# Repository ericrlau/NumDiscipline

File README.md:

# #DISCIPLINE (aka NumDiscipline)

A modified version of the great looking Discipline through hole keyboard design by coseyfannitutti to add numpad. 

## Modifications from original Discipline 

- Add numpad on right.
- Move arrow keys 0.25U down and right, similar to 1800 layout. 
- Adjust component layout on top of board, moving ATMega and buttons to the right, adding in more diodes in center. 
- Removed ~, Delete, Page Up, Page Down keys. These will be on alternate layer. 
- Created Digikey version of BOM, found here: https://octopart.com/bom-tool/AgAHKWUi

## ToDo 
- Adjust acrylic foot design to be wider, it looks a little thin. 
- add Via support
- Next order of PCBs: 
	- Adjust #DISCIPLINE logo in space bar area so that it doesn't overlap stablaizer. [Image](./images/knownIssues/Logoplacement.jpg)
	- Omit job number silk screen from vendor.[Plate](./images/knownIssues/plate.jpg) [Main](./images/knownIssues/jobNumMain.jpg) [Bottom](./images/knownIssues/jobNumBottom.jpg) 
	- Improve surface finish on black solder mask, some dark spots. [Image](./images/knownIssues/surfaceFinish.jpg) 
	- Remove drills from FR4 switch plate. [Image](./images/knownIssues/plate.jpg)

## Images

#### Prototype Build

#### Layout

#### Main PCB

#### FR4 Plate

#### Bottom PCB

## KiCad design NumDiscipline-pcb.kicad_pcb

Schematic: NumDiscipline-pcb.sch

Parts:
BOOT1: BOOT; SW_PUSH_6mm
C1, C2: 22p; C_Disc_D3.0mm_W1.6mm_P2.50mm
C3: 4.7u; CP_Radial_D4.0mm_P1.50mm
C4, C5: 0.1u; D_DO-35_SOD27_P5.08mm_Horizontal
D1, D2, D3, D4, D5, D6, D7, D8, D9, D10, D11, D12, D13, D14, D15, D16, D17, D18, D19, D20, D21, D22, D23, D24, D25, D26, D27, D28, D29, D30, D31, D32, D33, D34, D35, D36, D37, D38, D39, D40, D41, D42, D43, D44, D45, D46, D47, D48, D49, D50, D51, D52, D53, D54, D55, D56, D57, D58, D59, D60, D61, D62, D63, D64, D65, D66, D67, D68, D75, D76, D77, D78, D79, D80, D81, D82, D83, D84, D85, D86, D87: D_DO-35_SOD27_P5.08mm_Horizontal
D69, D70: 3.6V; D_DO-35_SOD27_P5.08mm_Horizontal
F1: 500mA; polyfuse_5.1mm
J1: AVR-ISP-6; AVR_ICSP_3x2
LED1: POWER; LED_D3.0mm
R1, R2: 5.1k; R_Axial_DIN0204_L3.6mm_D1.6mm_P7.62mm_Horizontal
R3, R4: 75R; R_Axial_DIN0204_L3.6mm_D1.6mm_P7.62mm_Horizontal
R5: 1.5k; R_Axial_DIN0204_L3.6mm_D1.6mm_P7.62mm_Horizontal
R6: 1.5K; R_Axial_DIN0204_L3.6mm_D1.6mm_P7.62mm_Horizontal
R7: 10k; R_Axial_DIN0204_L3.6mm_D1.6mm_P7.62mm_Horizontal
RESET1: RESET; SW_PUSH_6mm
SW1: ESCAPE; SW_Cherry_MX1A_1.00u_PCB-NOSCREEN
SW2: 1; SW_Cherry_MX1A_1.00u_PCB-NOSCREEN
SW3, SW4, SW5, SW6, SW7, SW8, SW9, SW10, SW11, SW12, SW13, SW15, SW17, SW18, SW19, SW20, SW21, SW22, SW23, SW24, SW25, SW26, SW27, SW28, SW30, SW32, SW33, SW34, SW35, SW36, SW37, SW38, SW39, SW40, SW41, SW42, SW44, SW46, SW47, SW48, SW49, SW50, SW51, SW52, SW53, SW54, SW55, SW57, SW58, SW62, SW65, SW66, SW67, SW68, SW72, SW75, SW76, SW77, SW78, SW79, SW81, SW82, SW83, SW84, SW86, SW87: KEYSW; SW_Cherry_MX1A_1.00u_PCB-NOSCREEN
SW14, SW80, SW85: KEYSW; SW_Cherry_MX1A_2.00u_PCBNOSCREEN
SW16, SW29, SW70, SW71, SW73, SW74: KEYSW; SW_Cherry_MX1A_1.50u_PCBNOSCREEN
SW31, SW56: KEYSW; SW_Cherry_MX1A_1.75u_PCBNOSCREEN
SW43, SW45: KEYSW; SW_Cherry_MX1A_2.25u_PCBNOSCREEN
SW59, SW60, SW61, SW63, SW64, SW69: KEYSW; SW_Cherry_MX1A_1.25u_PCBNOSCREEN
U1: ATmega32A-PU; DIP-40_W15.24mm
USB1: USB_C_GCT_USB4085
Y1: Crystal; Crystal_HC49-4H_Vertical

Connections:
+5V: C3.1, C4.1, C5.1, F1.1, J1.2, LED1.2 (A), R5.1, R7.1, U1.10, U1.30
D+: R4.1, U1.16
D-: R3.1, U1.17
GND: BOOT1.1, C1.2, C2.2, C3.2, C4.2, C5.2, D69.2 (A), D70.2 (A), J1.6, R1.1, R2.2, R6.2, RESET1.1, U1.11, U1.31, USB1.A1, USB1.A12, USB1.B1, USB1.B12, USB1.S1
MISO: J1.1, U1.7
MOSI: J1.4, U1.6
unnamed: C1.1, U1.13, Y1.1
unnamed: C2.1, U1.12, Y1.2
unnamed: D1.2 (A), SW1.2
unnamed: D2.2 (A), SW2.2
unnamed: D3.2 (A), SW3.2
unnamed: D4.2 (A), SW4.2
unnamed: D5.2 (A), SW5.2
unnamed: D6.2 (A), SW6.2
unnamed: D7.2 (A), SW7.2
unnamed: D8.2 (A), SW8.2
unnamed: D9.2 (A), SW9.2
unnamed: D10.2 (A), SW10.2
unnamed: D11.2 (A), SW11.2
unnamed: D12.2 (A), SW12.2
unnamed: D13.2 (A), SW13.2
unnamed: D14.2 (A), SW14.2
unnamed: D15.2 (A), SW15.2
unnamed: D16.2 (A), SW16.2
unnamed: D17.2 (A), SW17.2
unnamed: D18.2 (A), SW18.2
unnamed: D19.2 (A), SW19.2
unnamed: D20.2 (A), SW20.2
unnamed: D21.2 (A), SW21.2
unnamed: D22.2 (A), SW22.2
unnamed: D23.2 (A), SW23.2
unnamed: D24.2 (A), SW24.2
unnamed: D25.2 (A), SW25.2
unnamed: D26.2 (A), SW26.2
unnamed: D27.2 (A), SW27.2
unnamed: D28.2 (A), SW28.2
unnamed: D29.2 (A), SW29.2
unnamed: D30.2 (A), SW30.2
unnamed: D31.2 (A), SW31.2, SW69.2
unnamed: D32.2 (A), SW32.2
unnamed: D33.2 (A), SW33.2
unnamed: D34.2 (A), SW34.2
unnamed: D35.2 (A), SW35.2
unnamed: D36.2 (A), SW36.2
unnamed: D37.2 (A), SW37.2
unnamed: D38.2 (A), SW38.2
unnamed: D39.2 (A), SW39.2
unnamed: D40.2 (A), SW40.2
unnamed: D41.2 (A), SW41.2
unnamed: D42.2 (A), SW42.2
unnamed: D43.2 (A), SW43.2
unnamed: D44.2 (A), SW44.2
unnamed: D45.2 (A), SW45.2
unnamed: D46.2 (A), SW46.2
unnamed: D47.2 (A), SW47.2
unnamed: D48.2 (A), SW48.2
unnamed: D49.2 (A), SW49.2
unnamed: D50.2 (A), SW50.2
unnamed: D51.2 (A), SW51.2
unnamed: D52.2 (A), SW52.2
unnamed: D53.2 (A), SW53.2
unnamed: D54.2 (A), SW54.2
unnamed: D55.2 (A), SW55.2
unnamed: D56.2 (A), SW56.2
unnamed: D57.2 (A), SW57.2
unnamed: D58.2 (A), SW58.2
unnamed: D59.2 (A), SW59.2, SW70.2
unnamed: D60.2 (A), SW60.2
unnamed: D61.2 (A), SW61.2, SW71.2
unnamed: D62.2 (A), SW62.2, SW72.2
unnamed: D63.2 (A), SW63.2, SW73.2
unnamed: D64.2 (A), SW64.2, SW74.2
unnamed: D65.2 (A), SW65.2
unnamed: D66.2 (A), SW66.2
unnamed: D67.2 (A), SW67.2
unnamed: D68.2 (A), SW68.2
unnamed: D69.1 (K), R3.2, R5.2, USB1.A7, USB1.B7
unnamed: D70.1 (K), R4.2, USB1.A6, USB1.B6
unnamed: D75.2 (A), SW75.2
unnamed: D76.2 (A), SW76.2
unnamed: D77.2 (A), SW77.2
unnamed: D78.2 (A), SW78.2
unnamed: D79.2 (A), SW79.2
unnamed: D80.2 (A), SW80.2
unnamed: D81.2 (A), SW81.2
unnamed: D82.2 (A), SW82.2
unnamed: D83.2 (A), SW83.2
unnamed: D84.2 (A), SW84.2
unnamed: D85.2 (A), SW85.2
unnamed: D86.2 (A), SW86.2
unnamed: D87.2 (A), SW87.2
unnamed: LED1.1 (K), R6.1
unnamed: R1.2, USB1.A5
unnamed: R2.1, USB1.B5
SCK: J1.3, U1.8
VCC: F1.2, USB1.A4, USB1.A9, USB1.B4, USB1.B9
boot: BOOT1.2, U1.18
col0: SW1.1, SW16.1, SW31.1, SW45.1, SW59.1, SW69.1, SW70.1, U1.38
col1: SW2.1, SW17.1, SW32.1, SW60.1, U1.4
col2: SW3.1, SW18.1, SW33.1, SW46.1, SW61.1, SW71.1, U1.37
col3: SW4.1, SW19.1, SW34.1, SW47.1, U1.5
col4: SW5.1, SW20.1, SW35.1, SW48.1, U1.36
col5: SW6.1, SW21.1, SW36.1, SW49.1, U1.19
col6: SW7.1, SW22.1, SW37.1, SW50.1, SW62.1, SW72.1, U1.20
col7: SW8.1, SW23.1, SW38.1, SW51.1, U1.28
col8: SW9.1, SW24.1, SW39.1, SW52.1, U1.27
col9: SW10.1, SW25.1, SW40.1, SW53.1, SW63.1, SW73.1, U1.26
col10: SW11.1, SW26.1, SW41.1, SW54.1, SW64.1, SW74.1, U1.25
col11: SW12.1, SW27.1, SW42.1, SW55.1, SW68.1, U1.24
col12: SW13.1, SW28.1, SW56.1, SW65.1, U1.23
col13: SW14.1, SW29.1, SW43.1, SW57.1, SW66.1, U1.22
col14: SW15.1, SW30.1, SW44.1, SW58.1, SW67.1, U1.21
col15: SW75.1, SW78.1, SW81.1, SW83.1, SW86.1, U1.35
col16: SW76.1, SW79.1, SW82.1, SW84.1, SW87.1, U1.34
col17: SW77.1, SW80.1, SW85.1, U1.33
reset: J1.5, R7.2, RESET1.2, U1.9
row0: D1.1 (K), D2.1 (K), D3.1 (K), D4.1 (K), D5.1 (K), D6.1 (K), D7.1 (K), D8.1 (K), D9.1 (K), D10.1 (K), D11.1 (K), D12.1 (K), D13.1 (K), D14.1 (K), D15.1 (K), D75.1 (K), D76.1 (K), D77.1 (K), U1.3
row1: D16.1 (K), D17.1 (K), D18.1 (K), D19.1 (K), D20.1 (K), D21.1 (K), D22.1 (K), D23.1 (K), D24.1 (K), D25.1 (K), D26.1 (K), D27.1 (K), D28.1 (K), D29.1 (K), D30.1 (K), D78.1 (K), D79.1 (K), D80.1 (K), U1.39
row2: D31.1 (K), D32.1 (K), D33.1 (K), D34.1 (K), D35.1 (K), D36.1 (K), D37.1 (K), D38.1 (K), D39.1 (K), D40.1 (K), D41.1 (K), D42.1 (K), D43.1 (K), D44.1 (K), D81.1 (K), D82.1 (K), U1.2
row3: D45.1 (K), D46.1 (K), D47.1 (K), D48.1 (K), D49.1 (K), D50.1 (K), D51.1 (K), D52.1 (K), D53.1 (K), D54.1 (K), D55.1 (K), D56.1 (K), D57.1 (K), D58.1 (K), D83.1 (K), D84.1 (K), D85.1 (K), U1.40
row4: D59.1 (K), D60.1 (K), D61.1 (K), D62.1 (K), D63.1 (K), D64.1 (K), D65.1 (K), D66.1 (K), D67.1 (K), D68.1 (K), D86.1 (K), D87.1 (K), U1.1

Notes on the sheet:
DISCIPLINE // 65% keyboard with only through hole components
7/1/2019
DISCIPLINE

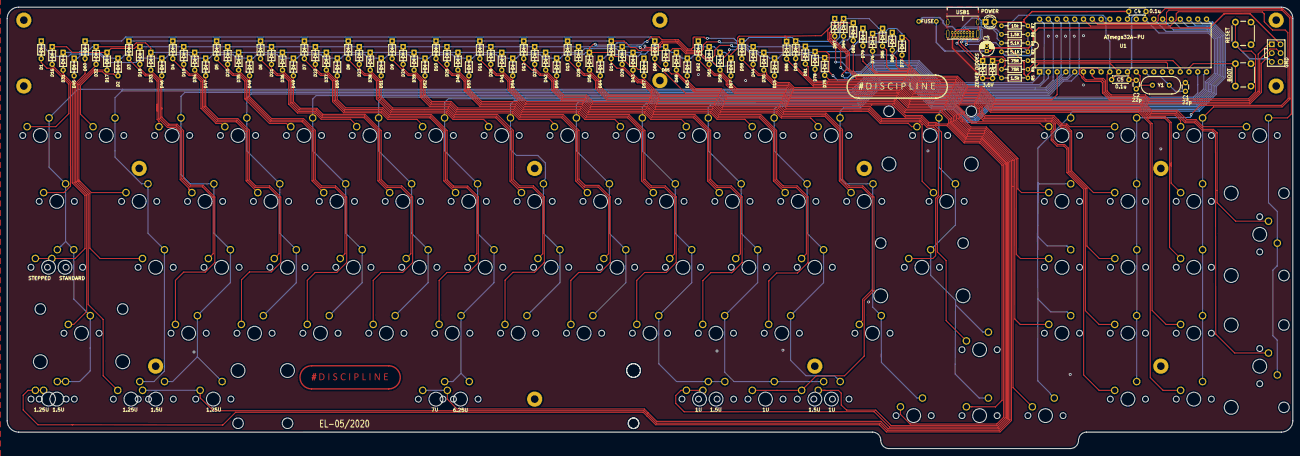
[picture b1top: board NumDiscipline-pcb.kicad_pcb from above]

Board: 2 copper layers, 371.6 x 127.6 mm, 191 parts (0 on the bottom side), 121 nets.

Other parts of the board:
ST62: 7U; MX-7U-Stabilizer

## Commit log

2020-04-26 initial commit from discipline
2020-04-26 added numpad to pcb, still need layout updates
2020-04-27 working on routing, renamed project file
2020-04-27 new routing fixed, ready for checkover
2020-04-27 update readme to add some info, still needs a lot of cleanup
2020-04-28 add plate
2020-04-28 add 3d, finish plate
2020-04-30 cleanup files, update readme, add gerbers
2020-04-30 format fix
2020-04-30 image in readme fix?
2020-04-30 format fix
    format fix
    format fix
    image in readme fix?
    image in readme fix?
2020-04-30 fix formating
2020-05-11 start making adjustments from first proto
2020-05-12 proto feedback incorperated
2020-05-14 order PCBs and ponoko
2020-05-16 update images
2020-05-16 add proto photo
2020-05-23 update readme after sample build
2020-05-23 add drill note on FR4 plate in readme
2020-06-14 update readme, new pictures
2020-06-14 remove old dxg files, new ones coming soon
